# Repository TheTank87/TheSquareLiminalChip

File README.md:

# TheSquareLiminalChip
A custom devboard that can be a replacement for the ESP and Rasberries.

# Description
This is a custom devboard meant to be like the ESPs and Rasberries. It has a USB-C port, flash memory, IOs, etc. Specifically this is a RP2040 devboard designed to be a versatile, low-cost microcontroller platform. Basically, I made my own microcontroller.
# Features
* USB-C Port
* I/O Headers
* RP2040 Rasberry Pi
* Flash Memory storage
* Crystal Oscillator

# BOM

|Item|Qty|Supplier|Cost|Link|
|-----|--|-------|-----|-----|
|Assembled Devboard|1|JLCPCB|$65.68|[Link](	https://jlcpcb.com/)|

# Schematic and PCB Design

The schematic design for this board is pretty straight forward. The top image is the finished product, but I had to overcome some serious errors in routing to get to this point. I don't know when or how, but I somehow flipped or wired the wrong ports! 

These are the parts that I messed up, which affected the SMD pads on my PCB board, which was a PAIN IN THE SOUTH POLE. I had to spend time diving through my own mess to clean everything up and even then, the footprints were ALSO WRONG. The SMD pads for some parts where in totally wrong positions and I needed to use exact positioning to put them in their place. This also took a long time. 

Then, just when I thought I was finished by pressing DRC, I got like 38 errors, so I had to then spend time to troubleshoot everything until I was left with 5 errors.

These errors were relatively easy to fix, all I had to do was make the thermal relief spokes 1 instead of 2 and it solved all my problems!

# Assembly and Conclusion

Since I was a beginner, this project was mainly learning and troubleshooting, and I think the troubleshooting part is really important to project in general as I was actually learning on how to solve problems. NOW, I need to assemble this thing by soldering and it ain't gonna be easy. The board is SMALL, like the size of my palm, so that's gonna be fun.

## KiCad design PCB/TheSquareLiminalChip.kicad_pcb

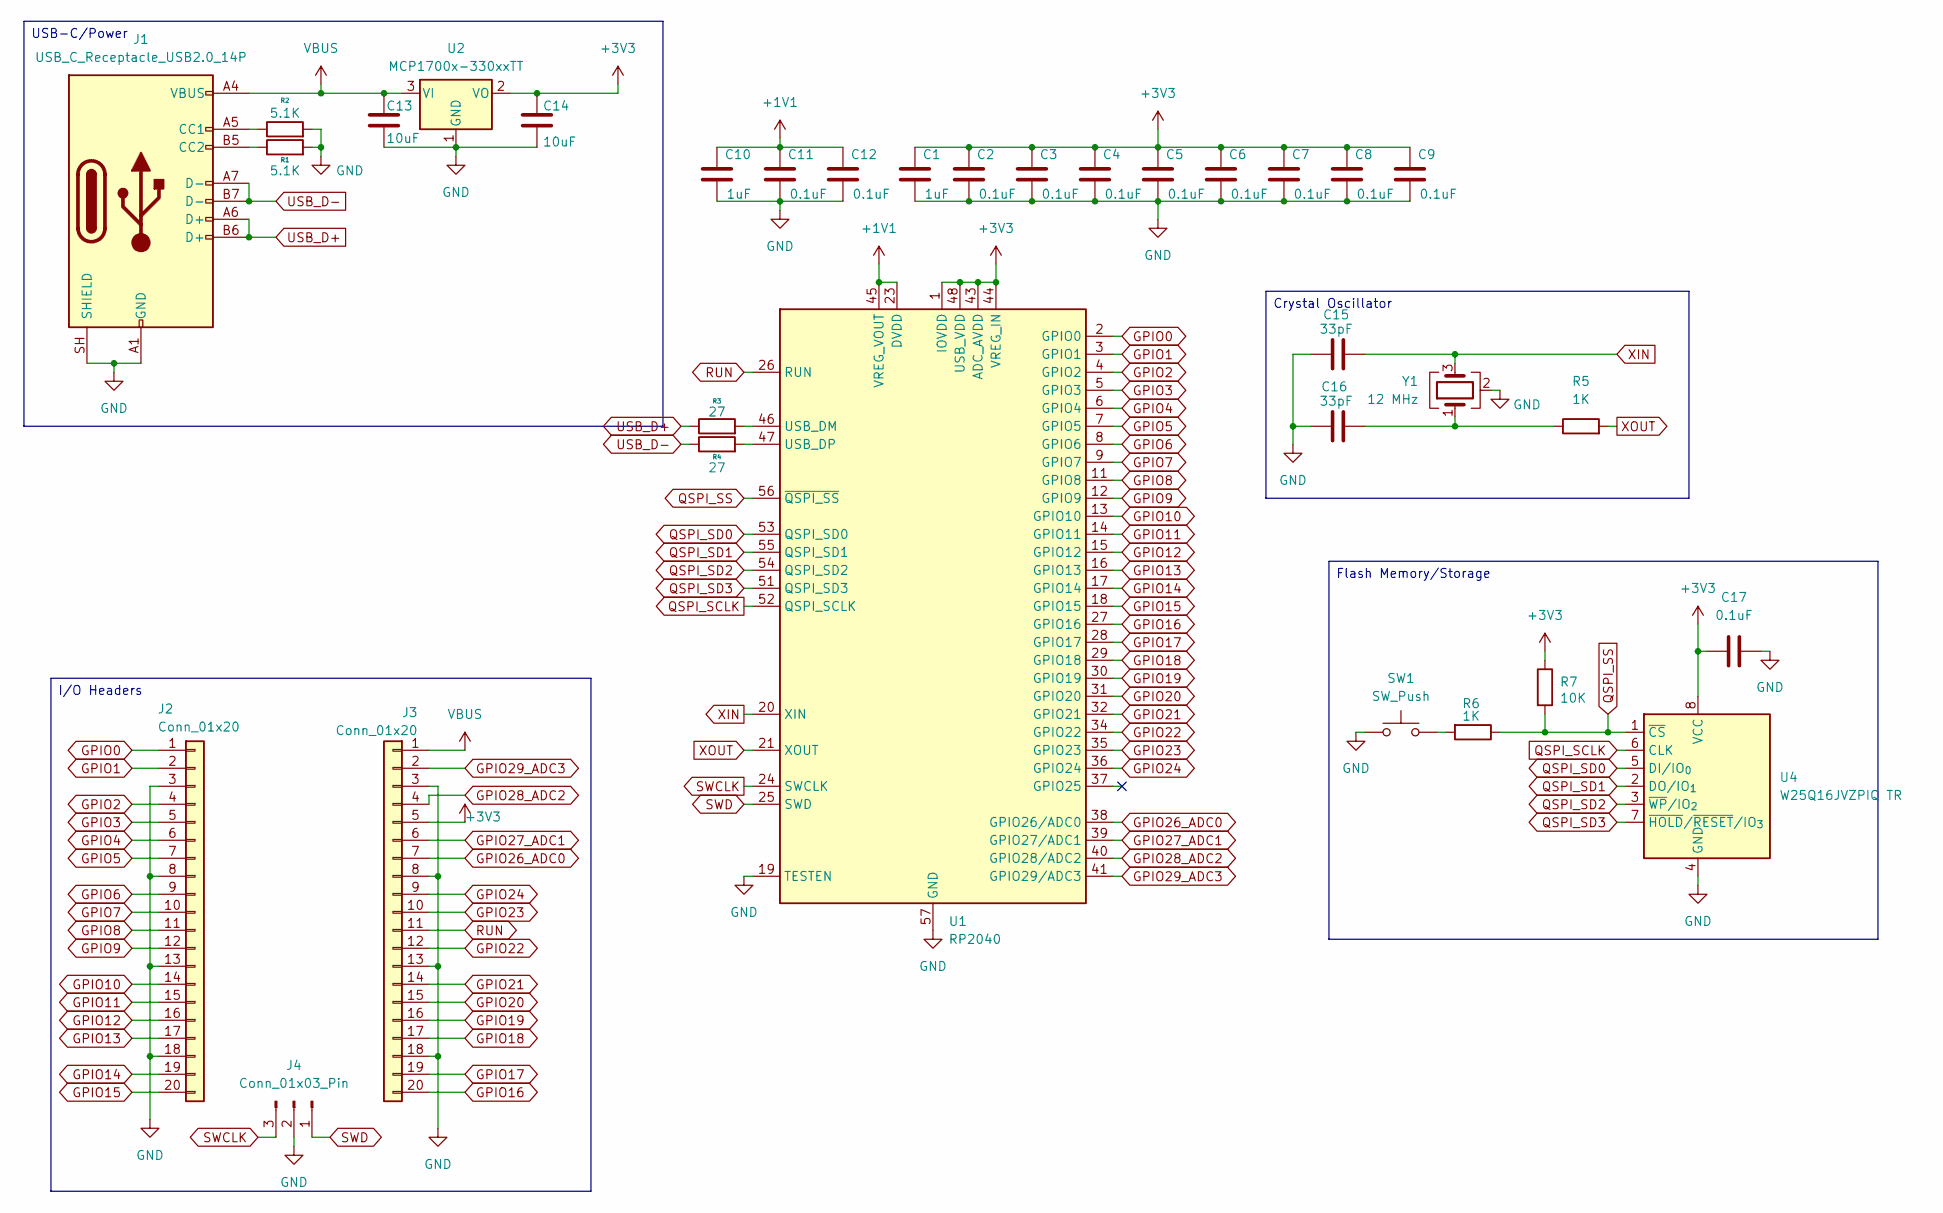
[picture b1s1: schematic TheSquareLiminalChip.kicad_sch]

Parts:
C1, C10: 1uF; C_0402_1005Metric
C2, C3, C4, C5, C6, C7, C8, C9, C11, C12, C17: 0.1uF; C_0402_1005Metric
C13, C14: 10uF; C_0603_1608Metric
C15, C16: 33pF; C_0402_1005Metric
J1: USB_C_Receptacle_USB2.0_14P; USB_C_Receptacle_HRO_TYPE-C-31-M-12
J2, J3: Conn_01x20; PinHeader_1x20_P2.54mm_Vertical
J4: Conn_01x03_Pin; PinHeader_1x03_P2.54mm_Vertical
R1, R2: 5.1K; R_0402_1005Metric
R3, R4: 27; R_0402_1005Metric
R5, R6: 1K; R_0402_1005Metric
R7: 10K; R_0402_1005Metric
SW1: SW_Push; SW_Push_SPST_NO_Alps_SKRK
U1: RP2040; QFN-56-1EP_7x7mm_P0.4mm_EP3.2x3.2mm
U2: MCP1700x-330xxTT; SOT-23
U4: W25Q16JVZPIQ TR; Winbond_USON-8-1EP_3x2mm_P0.5mm_EP0.2x1.6mm
Y1: 12 MHz; Crystal_SMD_3225-4Pin_3.2x2.5mm

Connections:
+1V1: C10.1, C11.1, C12.1, U1.23 (DVDD), U1.45 (VREG_VOUT), U1.50
+3V3: C1.1, C2.1, C3.1, C4.1, C5.1, C6.1, C7.1, C8.1, C9.1, C14.1, C17.1, J3.5, R7.1, U1.1 (IOVDD), U1.10, U1.22, U1.33, U1.42, U1.43 (ADC_AVDD), U1.44 (VREG_IN), U1.48 (USB_VDD), U1.49, U2.2 (VO), U4.8 (VCC)
GND: C1.2, C2.2, C3.2, C4.2, C5.2, C6.2, C7.2, C8.2, C9.2, C10.2, C11.2, C12.2, C13.2, C14.2, C15.1, C16.1, C17.2, J1.A1 (GND), J1.A12 (GND), J1.B1 (GND), J1.B12 (GND), J1.SH (SHIELD), J2.3, J2.8, J2.13, J2.18, J3.3, J3.8, J3.13, J3.18, J4.2, R1.2, R2.2, SW1.1, U1.19 (TESTEN), U1.57 (GND), U2.1 (GND), U4.4 (GND), Y1.2 (G), Y1.4 (G)
GPIO0: J2.1, U1.2 (GPIO0)
GPIO1: J2.2, U1.3 (GPIO1)
GPIO2: J2.4, U1.4 (GPIO2)
GPIO3: J2.5, U1.5 (GPIO3)
GPIO4: J2.6, U1.6 (GPIO4)
GPIO5: J2.7, U1.7 (GPIO5)
GPIO6: J2.9, U1.8 (GPIO6)
GPIO7: J2.10, U1.9 (GPIO7)
GPIO8: J2.11, U1.11 (GPIO8)
GPIO9: J2.12, U1.12 (GPIO9)
GPIO10: J2.14, U1.13 (GPIO10)
GPIO11: J2.15, U1.14 (GPIO11)
GPIO12: J2.16, U1.15 (GPIO12)
GPIO13: J2.17, U1.16 (GPIO13)
GPIO14: J2.19, U1.17 (GPIO14)
GPIO15: J2.20, U1.18 (GPIO15)
GPIO16: J3.20, U1.27 (GPIO16)
GPIO17: J3.19, U1.28 (GPIO17)
GPIO18: J3.17, U1.29 (GPIO18)
GPIO19: J3.16, U1.30 (GPIO19)
GPIO20: J3.15, U1.31 (GPIO20)
GPIO21: J3.14, U1.32 (GPIO21)
GPIO22: J3.12, U1.34 (GPIO22)
GPIO23: J3.10, U1.35 (GPIO23)
GPIO24: J3.9, U1.36 (GPIO24)
GPIO26_ADC0: J3.7, U1.38 (GPIO26/ADC0)
GPIO27_ADC1: J3.6, U1.39 (GPIO27/ADC1)
GPIO28_ADC2: J3.4, U1.40 (GPIO28/ADC2)
GPIO29_ADC3: J3.2, U1.41 (GPIO29/ADC3)
unnamed: C16.2, R5.1, Y1.1
unnamed: J1.A5 (CC1), R2.1
unnamed: J1.B5 (CC2), R1.1
unnamed: R6.2, SW1.2
unnamed: R3.2, U1.46 (USB_DM)
unnamed: R4.2, U1.47 (USB_DP)
QSPI_SCLK: U1.52 (QSPI_SCLK), U4.6 (CLK)
QSPI_SD0: U1.53 (QSPI_SD0), U4.5 (DI/IO_{0})
QSPI_SD1: U1.55 (QSPI_SD1), U4.2 (DO/IO_{1})
QSPI_SD2: U1.54 (QSPI_SD2), U4.3 (~WP/IO_{2})
QSPI_SD3: U1.51 (QSPI_SD3), U4.7 (~HOLD/~RESET/IO_{3})
QSPI_SS: R6.1, R7.2, U1.56 (~QSPI_SS), U4.1 (~CS)
RUN: J3.11, U1.26 (RUN)
SWCLK: J4.3, U1.24 (SWCLK)
SWD: J4.1, U1.25 (SWD)
USB_D+: J1.A6 (D+), J1.B6 (D+), R3.1
USB_D-: J1.A7 (D-), J1.B7 (D-), R4.1
VBUS: C13.1, J1.A4 (VBUS), J1.A9 (VBUS), J1.B4 (VBUS), J1.B9 (VBUS), J3.1, U2.3 (VI)
XIN: C15.2, U1.20 (XIN), Y1.3
XOUT: R5.2, U1.21 (XOUT)

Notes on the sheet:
USB-C/Power
Flash Memory/Storage
Crystal Oscillator
I/O Headers

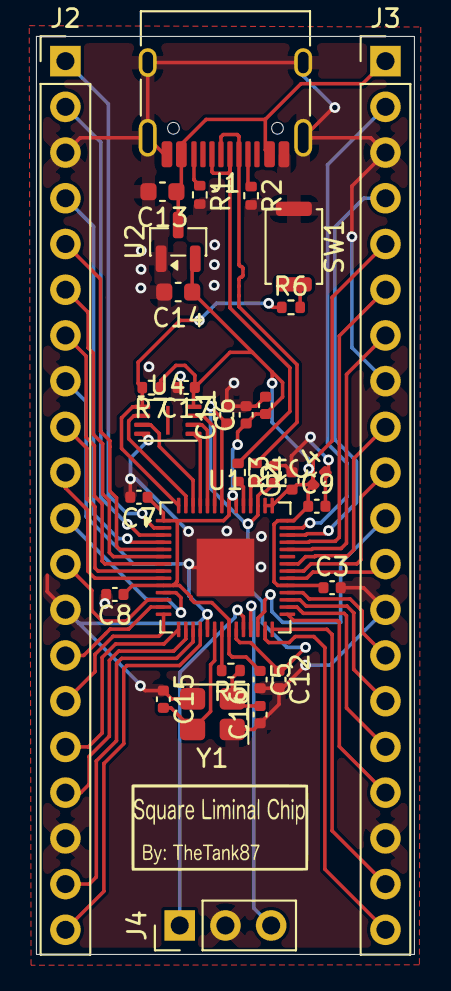
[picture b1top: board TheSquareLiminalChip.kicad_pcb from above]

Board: 2 copper layers, 21.0 x 51.0 mm, 33 parts (0 on the bottom side), 52 nets.

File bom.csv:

Designator,Footprint,Quantity,Comment,LCSC Part #
"C1, C10",402,2,1uF,
"C11, C12, C17, C2, C3, C4, C5, C6, C7, C8, C9",402,11,0.1uF,
"C13, C14",603,2,10uF,
"C15, C16",402,2,33pF,
J1,USB_C_Receptacle_HRO_TYPE-C-31-M-12,1,USB_C_Receptacle_USB2.0_14P,
"J2, J3",PinHeader_1x20_P2.54mm_Vertical,2,Conn_01x20,
J4,PinHeader_1x03_P2.54mm_Vertical,1,Conn_01x03_Pin,
"R1, R2",402,2,5.1K,
"R3, R4",402,2,27,
"R5, R6",402,2,1K,
R7,402,1,10K,
SW1,SW_Push_SPST_NO_Alps_SKRK,1,SW_Push,
U1,QFN-56-1EP_7x7mm_P0.4mm_EP3.2x3.2mm,1,RP2040,
U2,SOT-23,1,MCP1700x-330xxTT,
U4,Winbond_USON-8-1EP_3x2mm_P0.5mm_EP0.2x1.6mm,1,W25Q16JVZPIQ TR,
Y1,Crystal_SMD_3225-4Pin_3.2x2.5mm,1,12 MHz,
